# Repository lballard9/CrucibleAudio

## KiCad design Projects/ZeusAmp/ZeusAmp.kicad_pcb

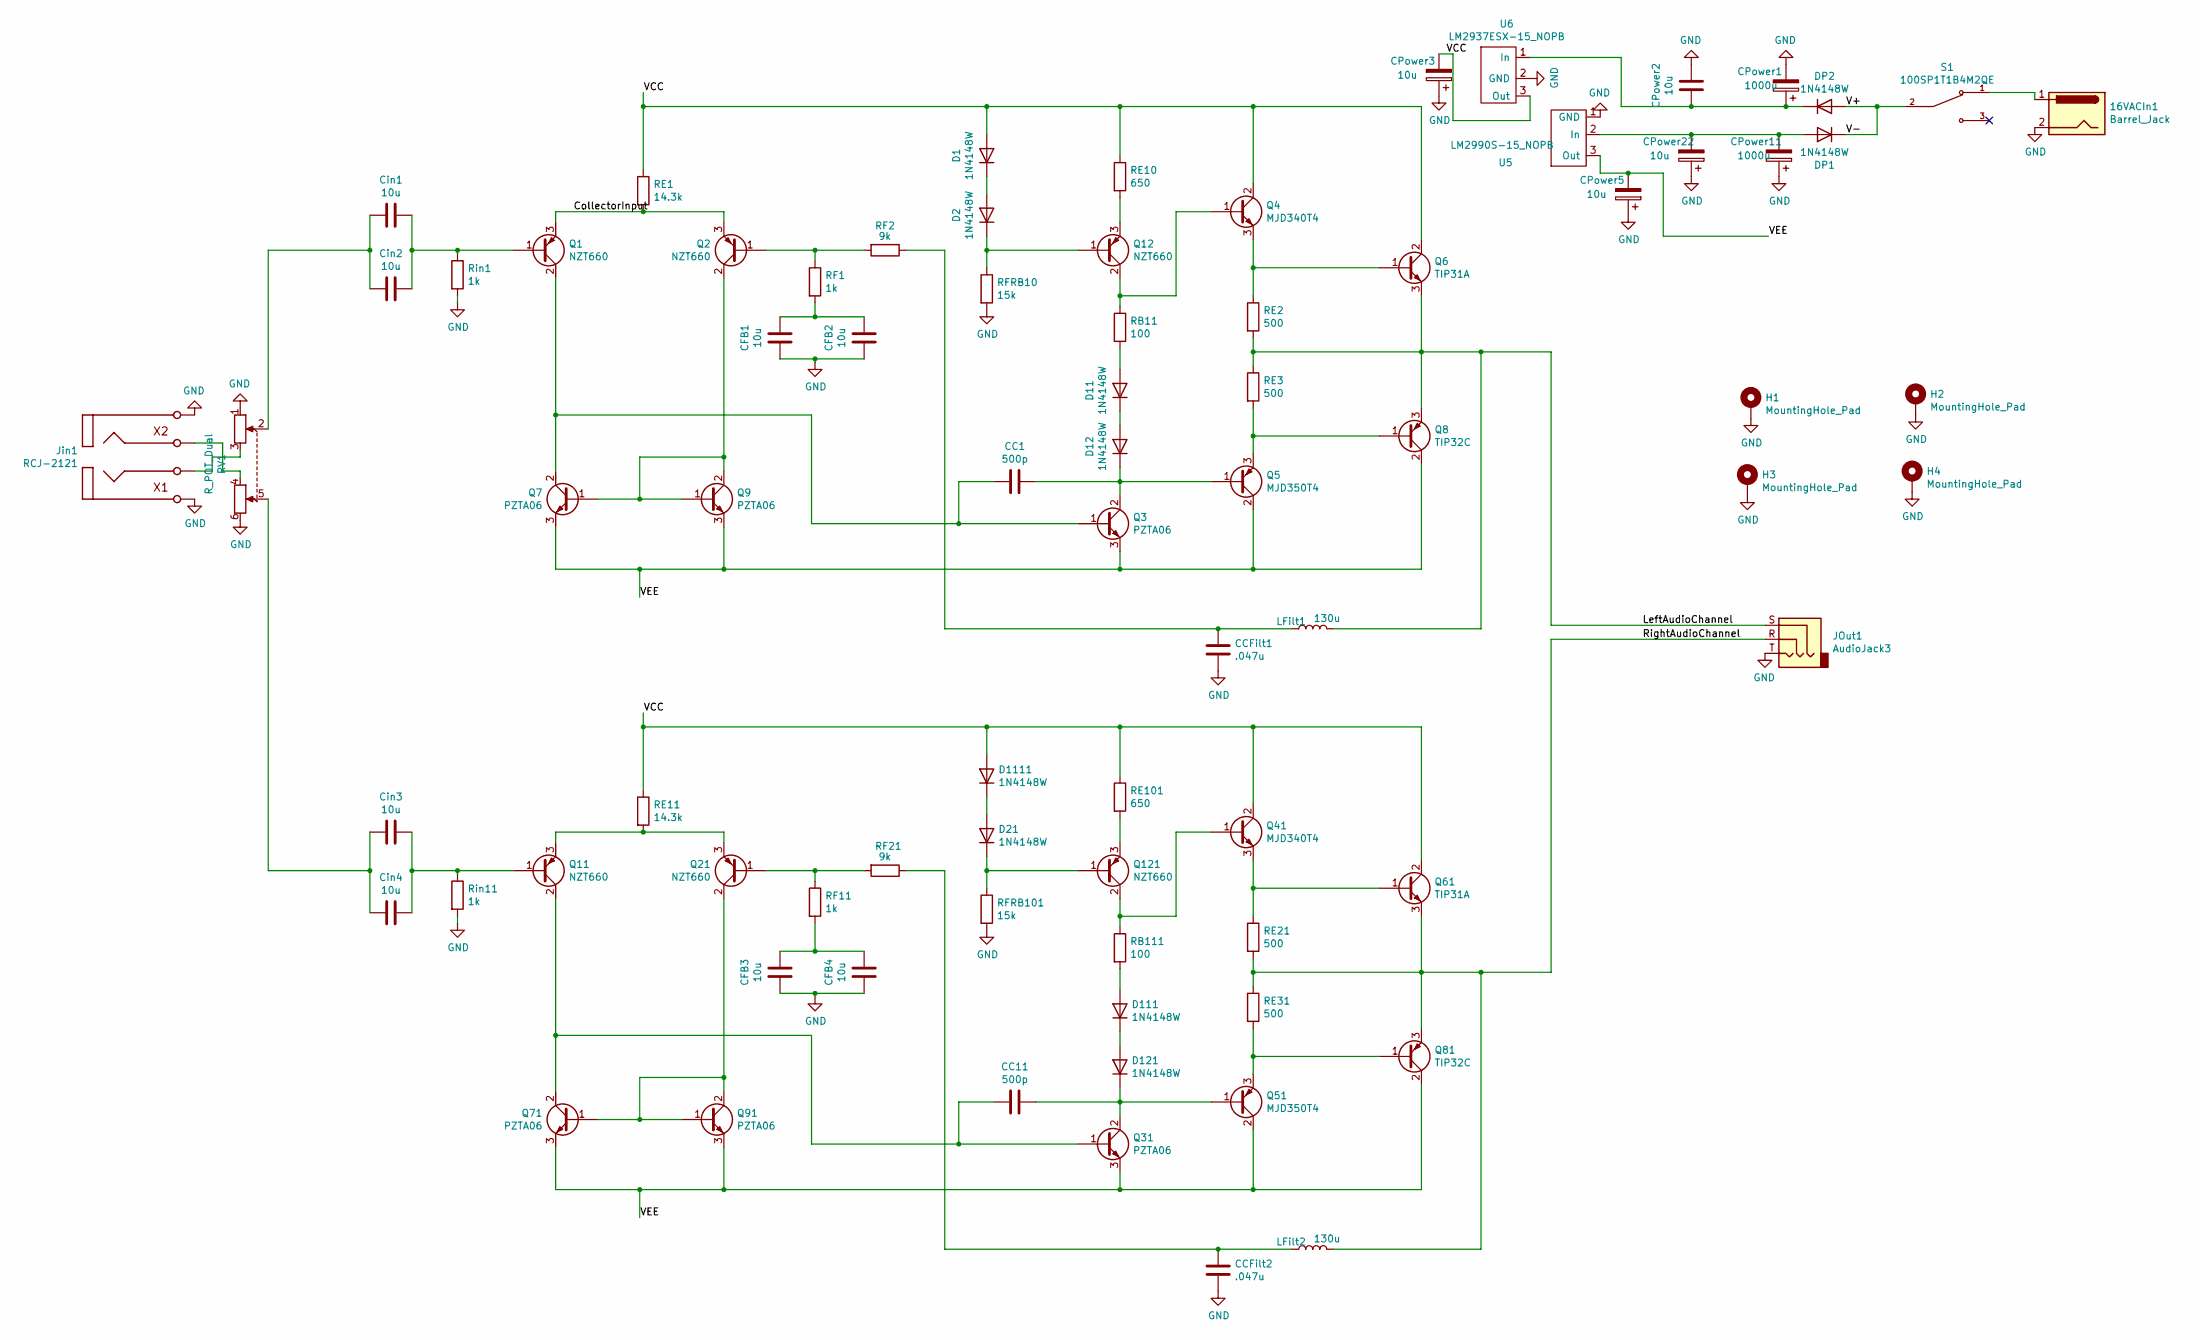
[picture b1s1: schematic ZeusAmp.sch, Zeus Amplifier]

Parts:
16VACIn1: Barrel_Jack; BarrelJack_Horizontal
CC1, CC11: 500p; C_1206_3216Metric
CCFilt1, CCFilt2: .047u; C_0805_2012Metric
CFB1, CFB2, CFB3, CFB4: 10u; C_0805_2012Metric
CPower1, CPower11: 1000u; CP_Radial_D13.0mm_P5.00mm
CPower2: 10u; C_0805_2012Metric
CPower3, CPower5, CPower22: 10u; CP_EIA-6032-28_Kemet-C
Cin1, Cin2, Cin3, Cin4: 10u; C_0805_2012Metric
D1, D2, D11, D12, D21, D111, D121, D1111: 1N4148W; D_SOD-123
DP1, DP2: 1N4148W; D_SOD-123
H1, H2, H3, H4: MountingHole_Pad; MountingHole_2.2mm_M2
JOut1: AudioJack3; Jack_3.5mm_CUI_SJ1-3533NG_Horizontal
Jin1: RCJ-2121
LFilt1, LFilt2: 130u; L_Axial_L26.0mm_D11.0mm_P7.62mm_Vertical_Fastron_77A
Q1, Q2, Q11, Q12, Q21, Q121: NZT660; SOT-223-3_TabPin2
Q3, Q7, Q9, Q31, Q71, Q91: PZTA06; SOT-223-3_TabPin2
Q4, Q41: MJD340T4; TO-252-2
Q5, Q51: MJD350T4; TO-252-2
Q6, Q61: TIP31A; TO-220-3_Vertical
Q8, Q81: TIP32C; TO-220-3_Vertical
RB11, RB111: 100; R_0805_2012Metric
RE1, RE11: 14.3k; R_0805_2012Metric
RE2, RE3, RE21, RE31: 500; R_0805_2012Metric
RE10, RE101: 650; R_0805_2012Metric
RF1, RF11: 1k; R_0805_2012Metric
RF2, RF21: 9k; R_0805_2012Metric
RFRB10, RFRB101: 15k; R_0805_2012Metric
RV1: R_POT_Dual; Potentiometer_Alps_RK09L_Double_Vertical
Rin1, Rin11: 1k; R_0805_2012Metric
S1: 100SP1T1B4M2QE; SW_100SP1T1B4M2QE; PARTREV E
U5: LM2990S-15_NOPB; TO-263-3_TabPin2
U6: LM2937ESX-15_NOPB; TO-263-3_TabPin2

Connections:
/CollectorInput: Q1.3 (E), Q2.3 (E), RE1.2
/LeftAudioChannel: JOut1.S, LFilt1.2, Q6.3 (E), Q8.3 (E), RE2.2, RE3.1
/RightAudioChannel: JOut1.R, LFilt2.2, Q61.3 (E), Q81.3 (E), RE21.2, RE31.1
/V+: DP1.1 (K), DP2.2 (A), S1.2
/VCC: CPower3.2, D1.2 (A), D1111.2 (A), Q4.2 (C), Q6.2 (C), Q41.2 (C), Q61.2 (C), RE1.1, RE10.1, RE11.1, RE101.1, U6.3 (Out)
/VEE: CPower5.2, Q3.3 (E), Q5.2 (C), Q7.3 (E), Q8.2 (C), Q9.3 (E), Q31.3 (E), Q51.2 (C), Q71.3 (E), Q81.2 (C), Q91.3 (E), U5.3 (Out)
GND: 16VACIn1.2, CCFilt1.1, CCFilt2.1, CFB1.1, CFB2.1, CFB3.1, CFB4.1, CPower1.2, CPower2.2, CPower3.1, CPower5.1, CPower11.1, CPower22.1, H1.1, H2.1, H3.1, H4.1, JOut1.T, Jin1.1, Jin1.3, RFRB10.2, RFRB101.2, RV1.1, RV1.6, Rin1.2, Rin11.2, U5.1 (GND), U6.2 (GND)
unnamed: 16VACIn1.1, S1.1
unnamed: CC1.1, Q1.2 (C), Q3.1 (B), Q7.2 (C)
unnamed: CC1.2, D12.1 (K), Q3.2 (C), Q5.1 (B)
unnamed: CC11.1, Q11.2 (C), Q31.1 (B), Q71.2 (C)
unnamed: CC11.2, D121.1 (K), Q31.2 (C), Q51.1 (B)
unnamed: CCFilt1.2, LFilt1.1, RF2.1
unnamed: CCFilt2.2, LFilt2.1, RF21.1
unnamed: CFB1.2, CFB2.2, RF1.2
unnamed: CFB3.2, CFB4.2, RF11.2
unnamed: CPower1.1, CPower2.1, DP2.1 (K), U6.1 (In)
unnamed: CPower11.2, CPower22.2, DP1.2 (A), U5.2 (In)
unnamed: Cin1.1, Cin2.1, RV1.2
unnamed: Cin1.2, Cin2.2, Q1.1 (B), Rin1.1
unnamed: Cin3.1, Cin4.1, RV1.5
unnamed: Cin3.2, Cin4.2, Q11.1 (B), Rin11.1
unnamed: D1.1 (K), D2.2 (A)
unnamed: D2.1 (K), Q12.1 (B), RFRB10.1
unnamed: D11.1 (K), D12.2 (A)
unnamed: D11.2 (A), RB11.2
unnamed: D21.1 (K), Q121.1 (B), RFRB101.1
unnamed: D111.1 (K), D121.2 (A)
unnamed: D111.2 (A), RB111.2
unnamed: D21.2 (A), D1111.1 (K)
unnamed: Jin1.2, RV1.3
unnamed: Jin1.4, RV1.4
unnamed: Q2.1 (B), RF1.1, RF2.2
unnamed: Q2.2 (C), Q7.1 (B), Q9.1 (B), Q9.2 (C)
unnamed: Q4.3 (E), Q6.1 (B), RE2.1
unnamed: Q5.3 (E), Q8.1 (B), RE3.2
unnamed: Q11.3 (E), Q21.3 (E), RE11.2
unnamed: Q4.1 (B), Q12.2 (C), RB11.1
unnamed: Q12.3 (E), RE10.2
unnamed: Q21.1 (B), RF11.1, RF21.2
unnamed: Q21.2 (C), Q71.1 (B), Q91.1 (B), Q91.2 (C)
unnamed: Q41.3 (E), Q61.1 (B), RE21.1
unnamed: Q51.3 (E), Q81.1 (B), RE31.2
unnamed: Q41.1 (B), Q121.2 (C), RB111.1
unnamed: Q121.3 (E), RE101.2

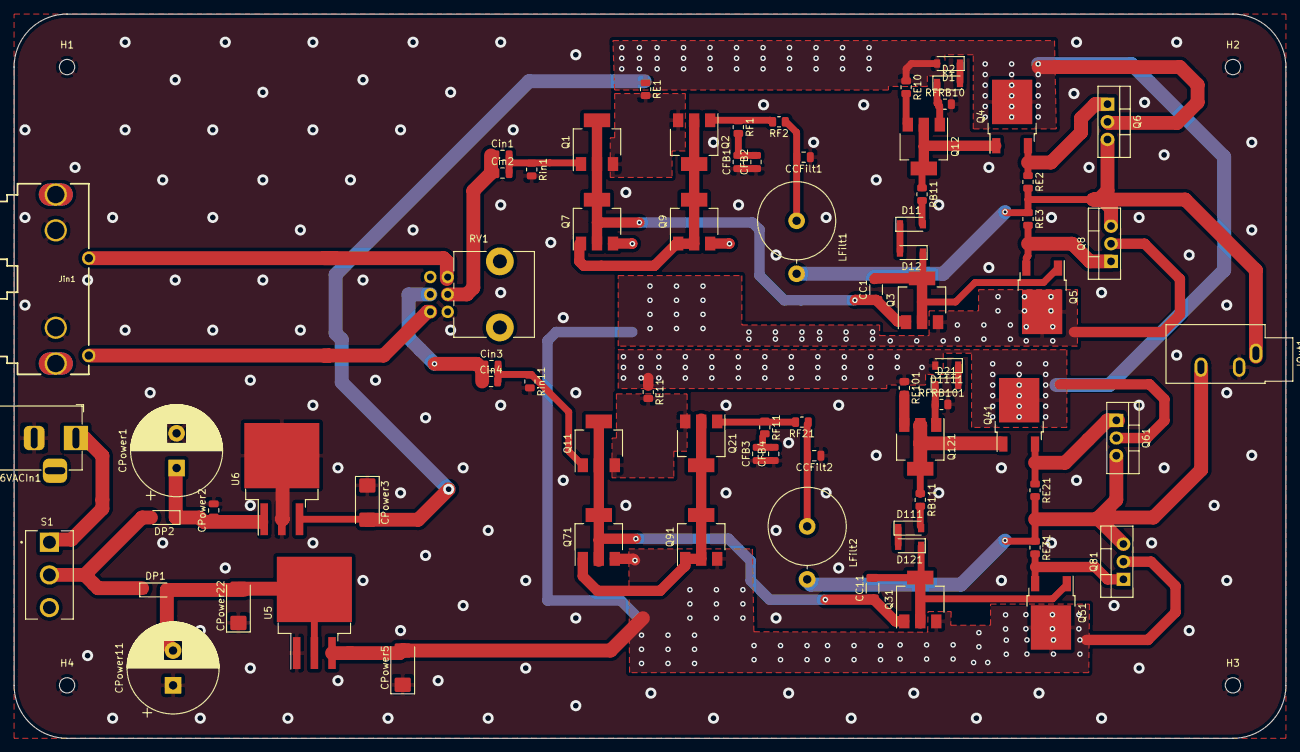
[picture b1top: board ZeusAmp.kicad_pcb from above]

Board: 2 copper layers, 182.9 x 104.1 mm, 79 parts (0 on the bottom side), 45 nets.

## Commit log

2021-03-10 added libaries
2021-03-10 hello world
2021-03-11 added spice file for Zeus V1
2021-03-11 added lowpass and changed the transistors to more up to date ones
2021-03-11 full schematic complete, layout only remaining step
2021-03-11 completed full layout, needs volume control pot and +-15V rails
2021-03-11 First Zeus V1 completed
2021-03-11 Fixed Power Supply Issue
2021-03-11 Fixed PSU in Spice as well
2021-03-11 small changes to the sheet properties
2021-03-11 Added some libraries
2021-03-12 Added Drill holes
2021-03-12 added switch
